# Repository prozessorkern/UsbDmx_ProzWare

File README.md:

# UsbDmx_ProzWare

Here you find the refactored hardware development (schematics and layout) of USB DMX from http://www.digital-enlightenment.de/usbdmx.htm.

Credit goes to Michael Dreschmann from http://www.digital-enlightenment.de.

This repo adds KiCad schematics and layout in SMD technology with a complete board design with onboard XLR connectors.

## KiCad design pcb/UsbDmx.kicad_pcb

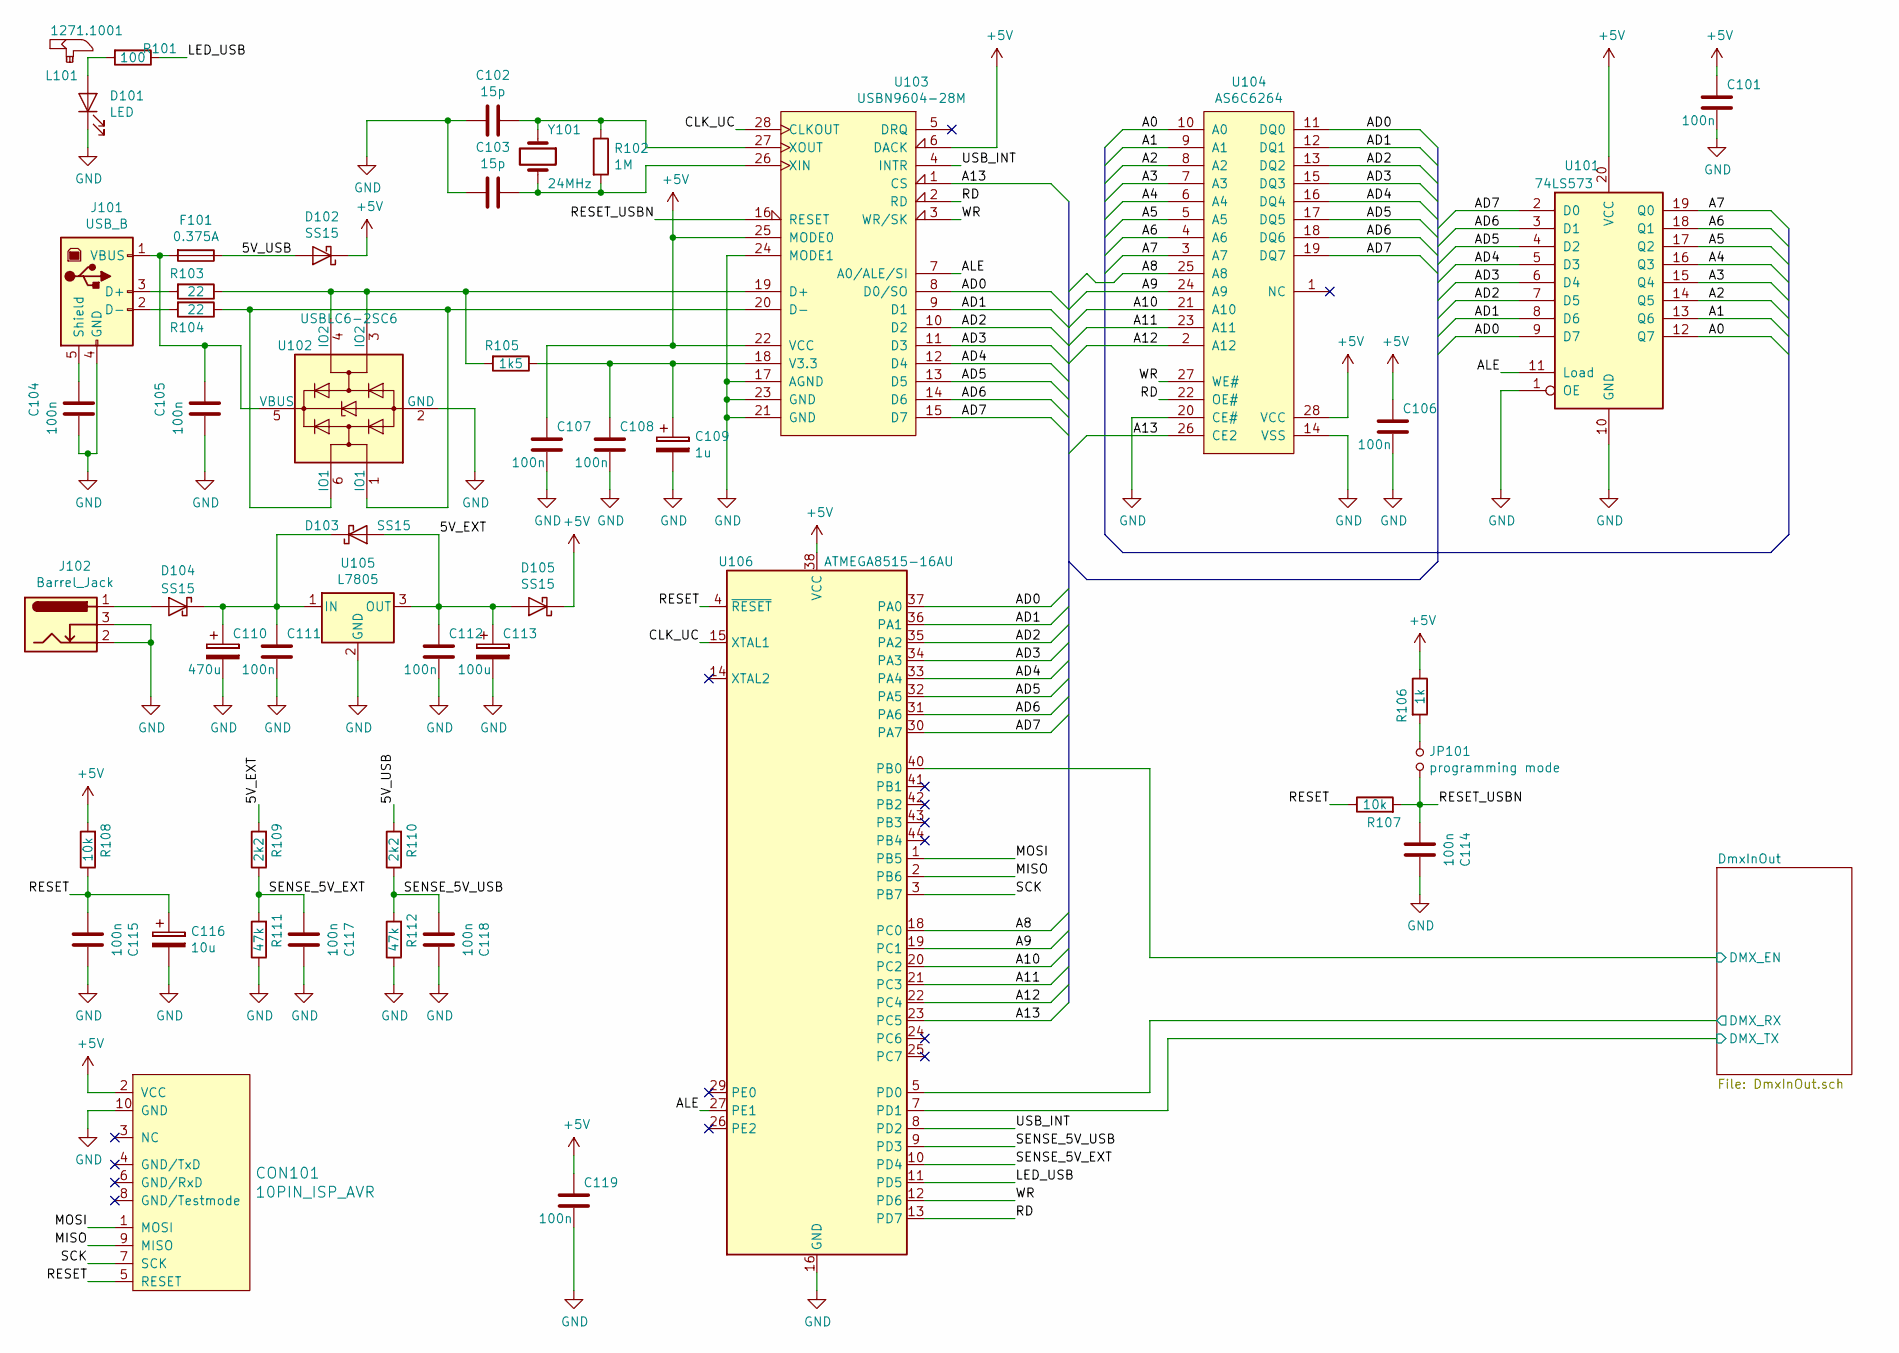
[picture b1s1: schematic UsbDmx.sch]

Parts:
C101, C106, C107, C108, C112, C114, C115, C117, C118, C119: 100n; C_0603_1608Metric_Pad1.05x0.95mm_HandSolder
C102, C103: 15p; C_0603_1608Metric_Pad1.05x0.95mm_HandSolder
C104, C105, C111: 100n; C_0805_2012Metric_Pad1.15x1.40mm_HandSolder
C109: 1u; CP_Radial_D4.0mm_P1.50mm
C110: 470u; CP_Radial_D10.0mm_P5.00mm
C113: 100u; CP_Radial_D6.3mm_P2.50mm
C116: 10u; CP_Radial_D5.0mm_P2.00mm
CON101: 10PIN_ISP_AVR; TC2050-IDC
D101: LED; LED_SMD_0603
D102, D103, D104, D105: SS15; D_SMA_Handsoldering
F101: 0.375A; Fuse_1206_3216Metric_Pad1.42x1.75mm_HandSolder
J101: USB_B; USB_B_OST_USB-B1HSxx_Horizontal
J102: Barrel_Jack; BARREL_JACK_CLIFF
JP101: programming mode; PinHeader_1x02_P2.54mm_Vertical
L101: 1271.1001
R101: 100; R_0603_1608Metric_Pad1.05x0.95mm_HandSolder
R102: 1M; R_0603_1608Metric_Pad1.05x0.95mm_HandSolder
R103, R104: 22; R_0603_1608Metric_Pad1.05x0.95mm_HandSolder
R105: 1k5; R_0603_1608Metric_Pad1.05x0.95mm_HandSolder
R106: 1k; R_0603_1608Metric_Pad1.05x0.95mm_HandSolder
R107, R108: 10k; R_0603_1608Metric_Pad1.05x0.95mm_HandSolder
R109, R110: 2k2; R_0603_1608Metric_Pad1.05x0.95mm_HandSolder
R111, R112: 47k; R_0603_1608Metric_Pad1.05x0.95mm_HandSolder
U101: 74LS573; SOIC-20W_7.5x12.8mm_P1.27mm
U102: USBLC6-2SC6; SOT-23-6
U103: USBN9604-28M; SOIC-28W_7.5x17.9mm_P1.27mm
U104: AS6C6264; SOIC-28W_8.7x18.7mm_Pitch1.27mm
U105: L7805; TO-263-2
U106: ATMEGA8515-16AU; TQFP-44_10x10mm_P0.8mm
Y101: 24MHz; Crystal_HC49-U_Vertical

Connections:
+5V: C101.1, C106.1, C107.1, C119.1, CON101.2 (VCC), D102.1 (K), D105.1 (K), R106.1, R108.2, U101.20 (VCC), U103.6 (DACK), U103.22 (VCC), U103.25 (MODE0), U104.28 (VCC), U106.38 (VCC); also elsewhere on the board
/5V_EXT: C112.1, C113.1, D103.2 (A), D105.2 (A), R109.2, U105.3 (OUT)
/5V_USB: D102.2 (A), F101.1, R110.2
/A0: U101.12 (Q7), U104.10 (A0)
/A1: U101.13 (Q6), U104.9 (A1)
/A2: U101.14 (Q5), U104.8 (A2)
/A3: U101.15 (Q4), U104.7 (A3)
/A4: U101.16 (Q3), U104.6 (A4)
/A5: U101.17 (Q2), U104.5 (A5)
/A6: U101.18 (Q1), U104.4 (A6)
/A7: U101.19 (Q0), U104.3 (A7)
/A8: U104.25 (A8), U106.18 (PC0)
/A9: U104.24 (A9), U106.19 (PC1)
/A10: U104.21 (A10), U106.20 (PC2)
/A11: U104.23 (A11), U106.21 (PC3)
/A12: U104.2 (A12), U106.22 (PC4)
/A13: U103.1 (CS), U104.26 (CE2), U106.23 (PC5)
/AD0: U101.9 (D7), U103.8 (D0/SO), U104.11 (DQ0), U106.37 (PA0)
/AD1: U101.8 (D6), U103.9 (D1), U104.12 (DQ1), U106.36 (PA1)
/AD2: U101.7 (D5), U103.10 (D2), U104.13 (DQ2), U106.35 (PA2)
/AD3: U101.6 (D4), U103.11 (D3), U104.15 (DQ3), U106.34 (PA3)
/AD4: U101.5 (D3), U103.12 (D4), U104.16 (DQ4), U106.33 (PA4)
/AD5: U101.4 (D2), U103.13 (D5), U104.17 (DQ5), U106.32 (PA5)
/AD6: U101.3 (D1), U103.14 (D6), U104.18 (DQ6), U106.31 (PA6)
/AD7: U101.2 (D0), U103.15 (D7), U104.19 (DQ7), U106.30 (PA7)
/ALE: U101.11 (Load), U103.7 (A0/ALE/SI), U106.27 (PE1)
/CLK_UC: U103.28 (CLKOUT), U106.15 (XTAL1)
/DmxInOut/DMX_EN: U106.40 (PB0); also elsewhere on the board
/DmxInOut/DMX_RX: U106.5 (PD0); also elsewhere on the board
/DmxInOut/DMX_TX: U106.7 (PD1); also elsewhere on the board
/LED_USB: R101.1, U106.11 (PD5)
/MISO: CON101.9 (MISO), U106.2 (PB6)
/MOSI: CON101.1 (MOSI), U106.1 (PB5)
/RD: U103.2 (RD), U104.22 (OE#), U106.13 (PD7)
/RESET: C115.2, C116.1, CON101.5 (RESET), R107.1, R108.1, U106.4 (~RESET)
/RESET_USBN: C114.2, JP101.2, R107.2, U103.16 (RESET)
/SCK: CON101.7 (SCK), U106.3 (PB7)
/SENSE_5V_EXT: C117.2, R109.1, R111.2, U106.10 (PD4)
/SENSE_5V_USB: C118.2, R110.1, R112.2, U106.9 (PD3)
/USB_INT: U103.4 (INTR), U106.8 (PD2)
/WR: U103.3 (WR/SK), U104.27 (WE#), U106.12 (PD6)
GND: C101.2, C102.2, C103.2, C104.2, C105.2, C106.2, C107.2, C108.2, C109.2, C110.2, C111.2, C112.2, C113.2, C114.1, C115.1, C116.2, C117.1, C118.1, C119.2, CON101.10 (GND), D101.1 (K), J101.4 (GND), J102.2, J102.3, R111.1, R112.1, U101.1 (OE), U101.10 (GND), U102.2 (GND), U103.17 (AGND), U103.21 (GND), U103.23 (GND), U103.24 (MODE1), U104.14 (VSS), U104.20 (CE#), U105.2 (GND), U106.16 (GND); also elsewhere on the board
unnamed: C102.1, R102.1, U103.27 (XOUT), Y101.1
unnamed: C103.1, R102.2, U103.26 (XIN), Y101.2
unnamed: C104.1, J101.5 (Shield)
unnamed: C105.1, F101.2, J101.1 (VBUS), U102.5 (VBUS)
unnamed: C108.1, C109.1, R105.1, U103.18 (V3.3)
unnamed: C110.1, C111.1, D103.1 (K), D104.1 (K), U105.1 (IN)
unnamed: D101.2 (A), R101.2
unnamed: D104.2 (A), J102.1
unnamed: J101.2 (D-), R104.2
unnamed: J101.3 (D+), R103.2
unnamed: JP101.1, R106.2
unnamed: R103.1, R105.2, U102.3 (IO2), U102.4 (IO2), U103.19 (D+)
unnamed: R104.1, U102.1 (IO1), U102.6 (IO1), U103.20 (D-)

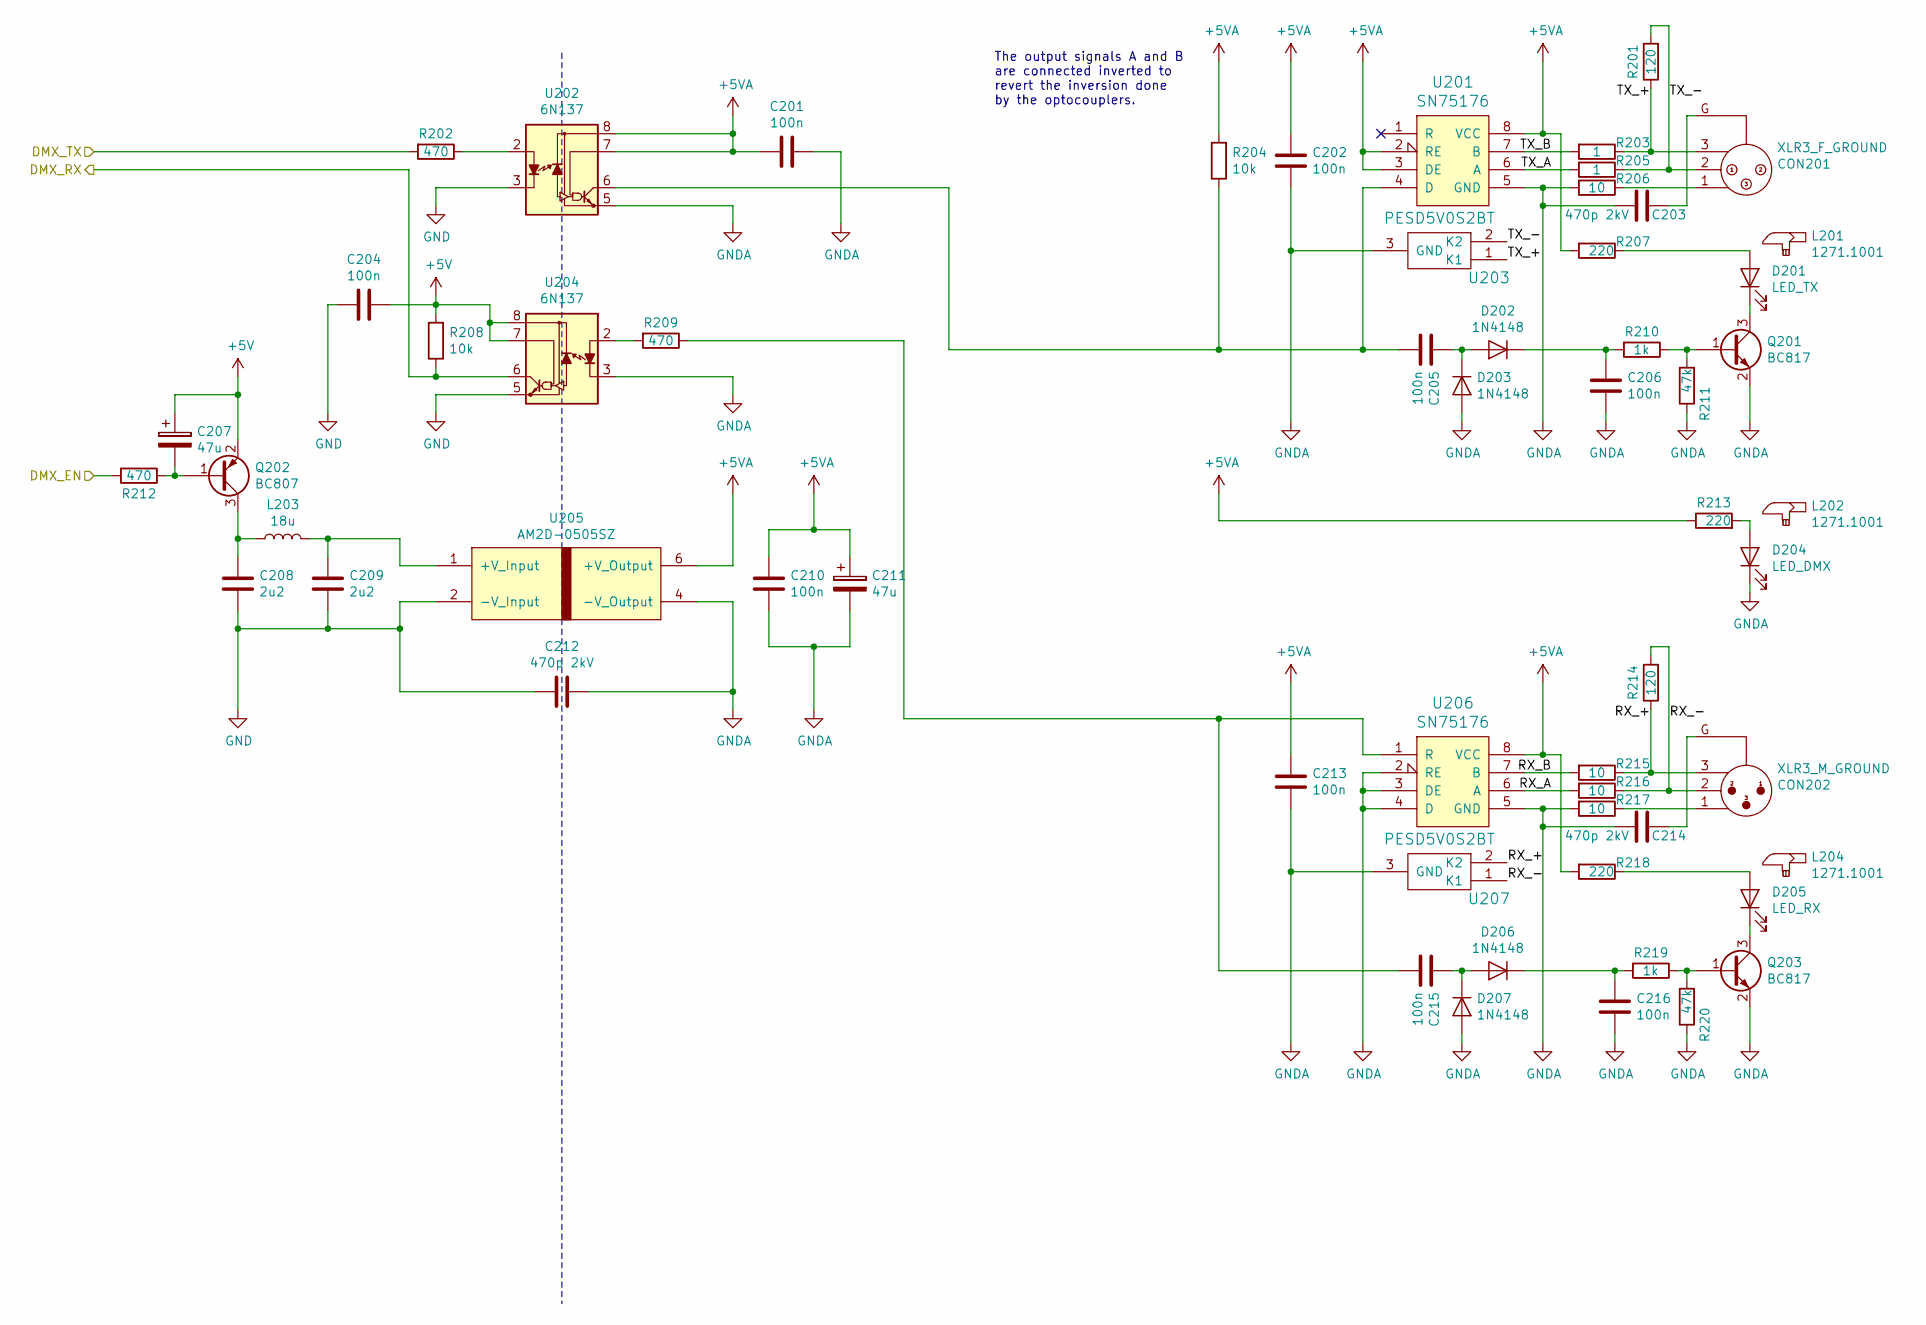
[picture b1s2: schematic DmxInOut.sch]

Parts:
C201, C202, C204, C205, C206, C210, C213, C215, C216: 100n; C_0603_1608Metric_Pad1.05x0.95mm_HandSolder
C203, C212, C214: 470p 2kV; C_Disc_D7.5mm_W5.0mm_P7.50mm
C207, C211: 47u; CP_Radial_D5.0mm_P2.00mm
C208, C209: 2u2; C_0805_2012Metric_Pad1.15x1.40mm_HandSolder
CON201: XLR3_F_GROUND; NC3FAH2_XLR_F
CON202: XLR3_M_GROUND; NC3MAH_XLR_M
D201: LED_TX; LED_SMD_0603
D202, D203, D206, D207: 1N4148; D_MiniMELF
D204: LED_DMX; LED_SMD_0603
D205: LED_RX; LED_SMD_0603
L201, L202, L204: 1271.1001
L203: 18u; inductor_1812
Q201, Q203: BC817; SOT-23
Q202: BC807; SOT-23
R201, R214: 120; R_MiniMELF_MMA-0204
R202, R209, R212: 470; R_0603_1608Metric_Pad1.05x0.95mm_HandSolder
R203, R205: 1; R_MiniMELF_MMA-0204
R204, R208: 10k; R_0603_1608Metric_Pad1.05x0.95mm_HandSolder
R206, R215, R216, R217: 10; R_MiniMELF_MMA-0204
R207, R213, R218: 220; R_0603_1608Metric_Pad1.05x0.95mm_HandSolder
R210, R219: 1k; R_0603_1608Metric_Pad1.05x0.95mm_HandSolder
R211, R220: 47k; R_0603_1608Metric_Pad1.05x0.95mm_HandSolder
U201, U206: SN75176; SO-8_3.9x4.9mm_P1.27mm
U202, U204: 6N137; GULLWING_8
U203, U207: PESD5V0S2BT; SOT-23_Handsoldering
U205: AM2D-0505SZ; SIP7

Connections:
+5V: C204.1, C207.1, Q202.2 (E), R208.2, U204.7, U204.8; also elsewhere on the board
+5VA: C201.2, C202.2, C210.2, C211.1, C213.2, R204.2, R207.2, R213.1, R218.2, U201.2 (RE), U201.3 (DE), U201.8 (VCC), U202.7, U202.8, U205.6 (+V_Output), U206.8 (VCC)
/DmxInOut/DMX_EN: R212.2; also elsewhere on the board
/DmxInOut/DMX_RX: R208.1, U204.6; also elsewhere on the board
/DmxInOut/DMX_TX: R202.2; also elsewhere on the board
/DmxInOut/RX_+: CON202.3, R214.1, R215.1, U207.2 (K2)
/DmxInOut/RX_-: CON202.2, R214.2, R216.1, U207.1 (K1)
/DmxInOut/RX_A: R216.2, U206.6 (A)
/DmxInOut/RX_B: R215.2, U206.7 (B)
/DmxInOut/TX_+: CON201.3, R201.1, R203.1, U203.1 (K1)
/DmxInOut/TX_-: CON201.2, R201.2, R205.1, U203.2 (K2)
/DmxInOut/TX_A: R205.2, U201.6 (A)
/DmxInOut/TX_B: R203.2, U201.7 (B)
GND: C204.2, C208.2, C209.2, C212.2, U202.3, U204.5, U205.2 (-V_Input); also elsewhere on the board
GNDA: C201.1, C202.1, C203.2, C206.1, C210.1, C211.2, C212.1, C213.1, C214.2, C216.1, D203.2 (A), D204.1 (K), D207.2 (A), Q201.2 (E), Q203.2 (E), R206.2, R211.1, R217.2, R220.1, U201.5 (GND), U202.5, U203.3 (GND), U204.3, U205.4 (-V_Output), U206.2 (RE), U206.3 (DE), U206.4 (D), U206.5 (GND), U207.3 (GND)
unnamed: C203.1, CON201.G
unnamed: C205.1, R204.1, U201.4 (D), U202.6
unnamed: C205.2, D202.2 (A), D203.1 (K)
unnamed: C206.2, D202.1 (K), R210.2
unnamed: C207.2, Q202.1 (B), R212.1
unnamed: C208.1, L203.1, Q202.3 (C)
unnamed: C209.1, L203.2, U205.1 (+V_Input)
unnamed: C214.1, CON202.G
unnamed: C215.1, R209.1, U206.1 (R)
unnamed: C215.2, D206.2 (A), D207.1 (K)
unnamed: C216.2, D206.1 (K), R219.2
unnamed: CON201.1, R206.1
unnamed: CON202.1, R217.1
unnamed: D201.1 (K), Q201.3 (C)
unnamed: D201.2 (A), R207.1
unnamed: D204.2 (A), R213.2
unnamed: D205.1 (K), Q203.3 (C)
unnamed: D205.2 (A), R218.1
unnamed: Q201.1 (B), R210.1, R211.2
unnamed: Q203.1 (B), R219.1, R220.2
unnamed: R202.1, U202.2
unnamed: R209.2, U204.2

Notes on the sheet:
The output signals A and B are connected inverted to revert the inversion done by the optocouplers.

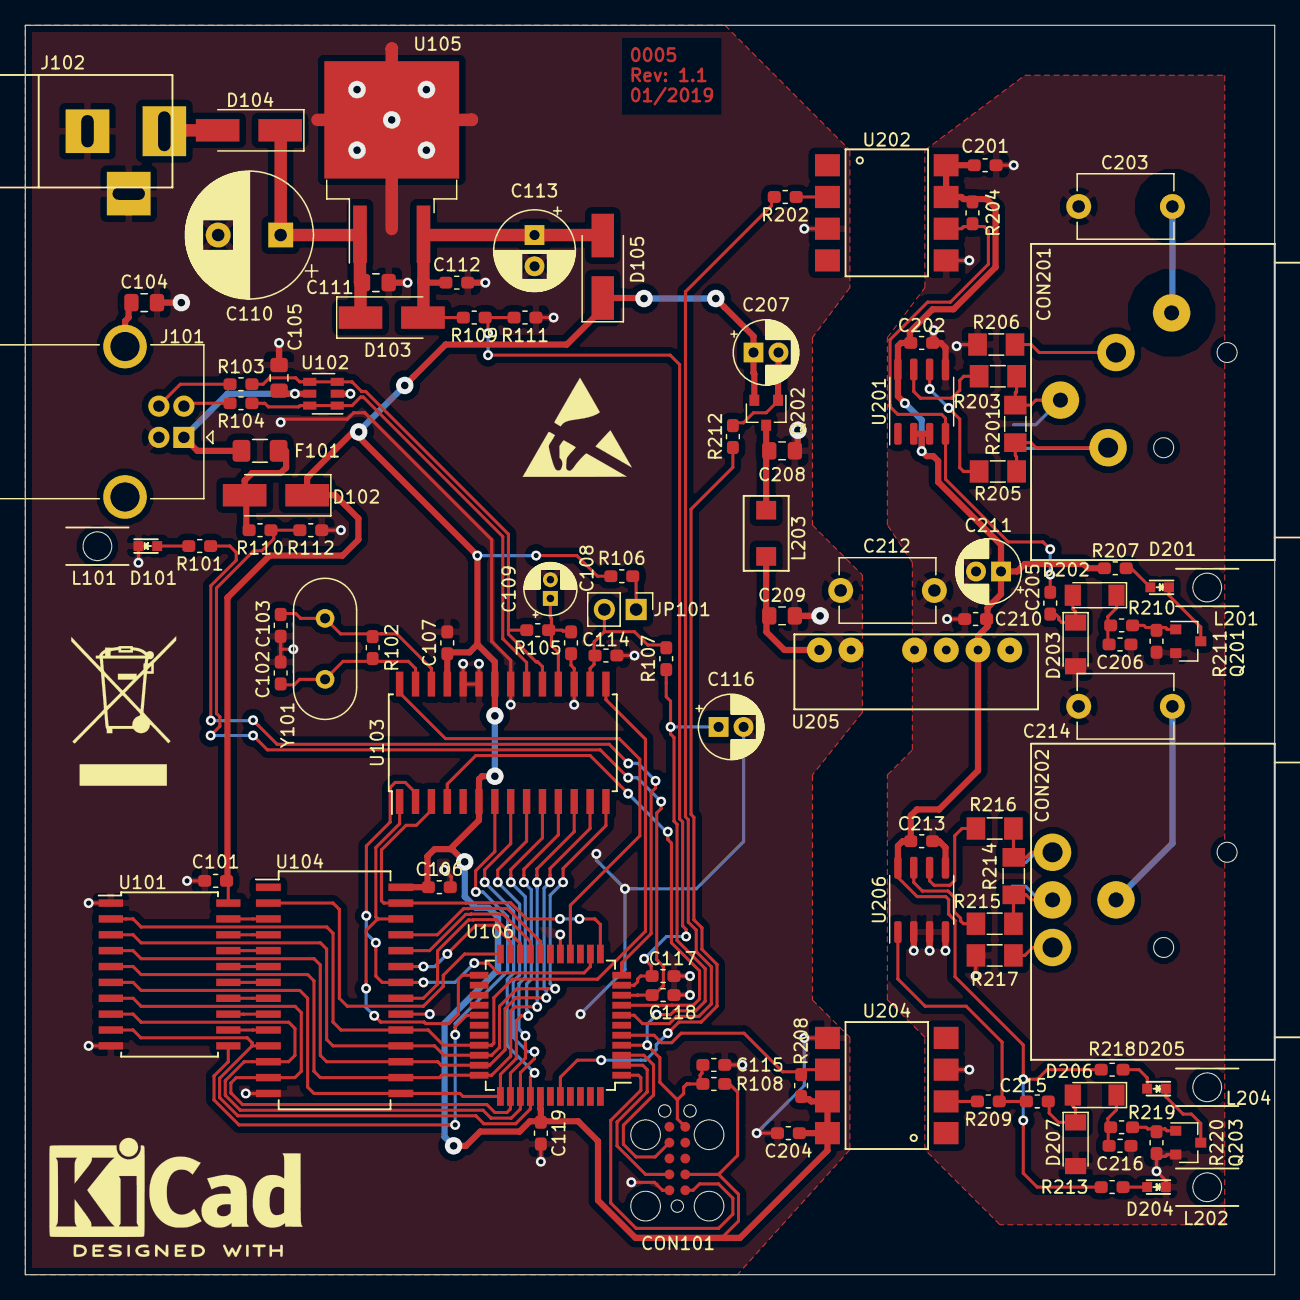
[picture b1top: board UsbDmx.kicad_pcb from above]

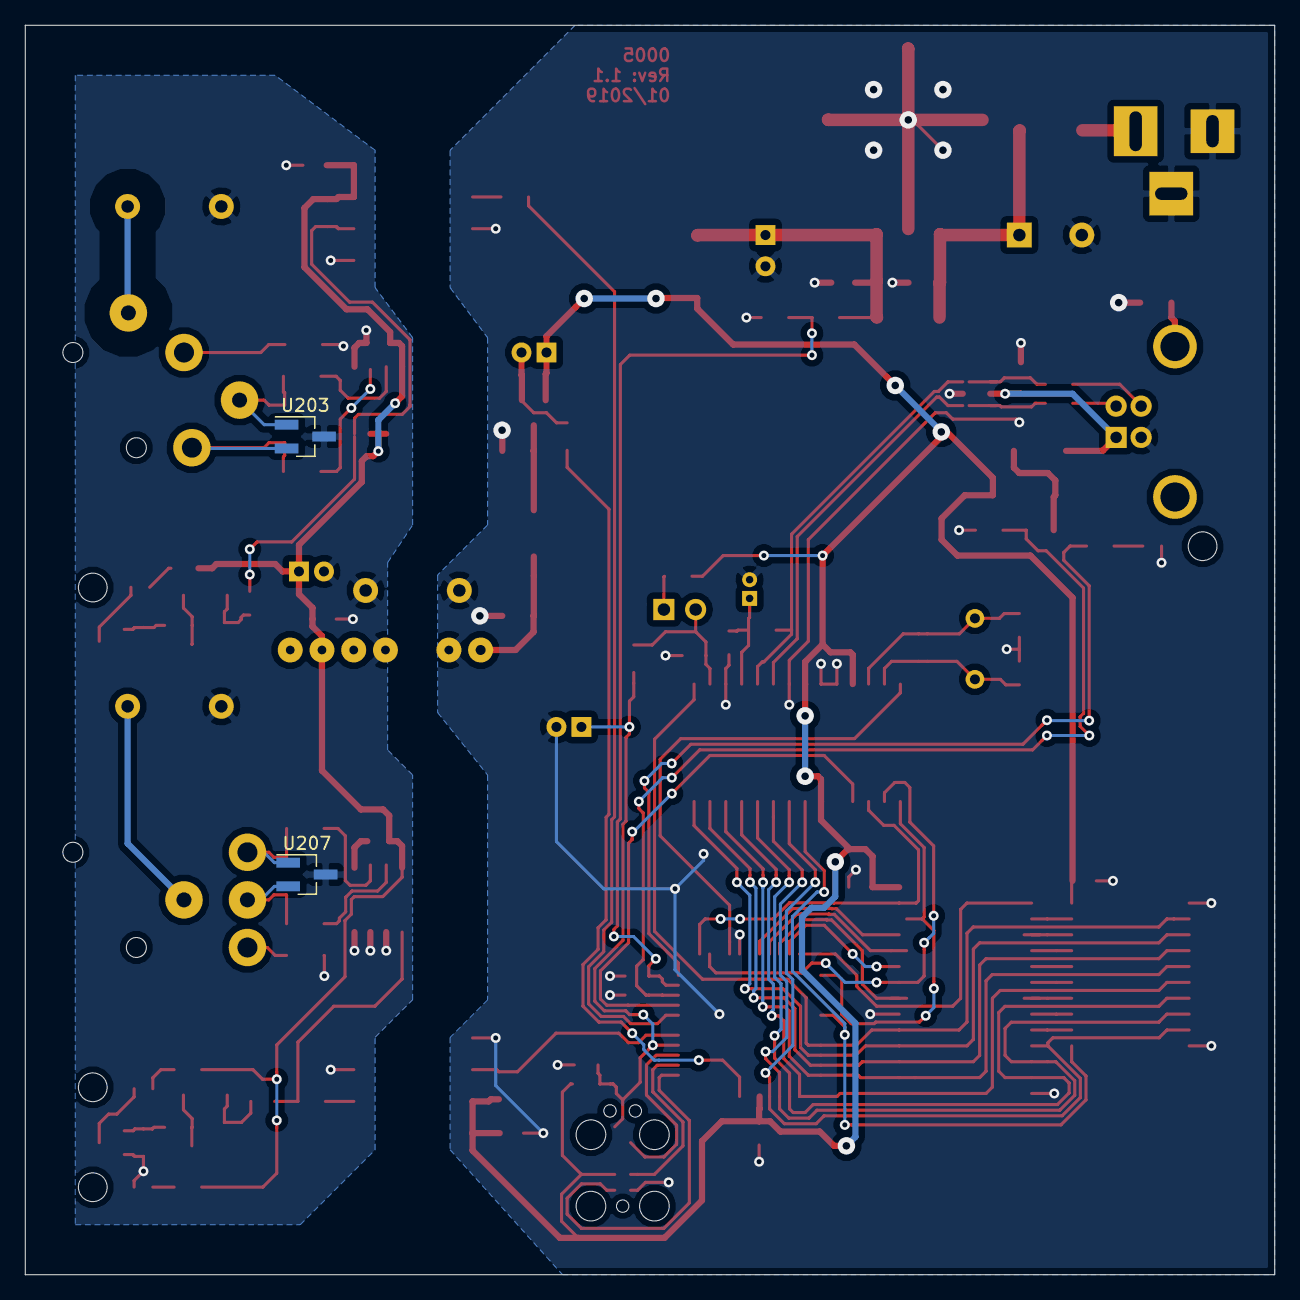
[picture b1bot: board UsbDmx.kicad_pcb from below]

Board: 2 copper layers, 100.0 x 100.0 mm, 108 parts (2 on the bottom side), 87 nets.

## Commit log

2018-11-24 Added the KiCad project with the nearly finished schematics
2018-11-25 Started footprint association
2018-11-27 finished footprint association
2018-12-18 startet layouting
    Startet to create a Layout
2018-12-20 Finished layout
    Added esd protection diodes to the dmx interface
    Routed everything
    added ground planes
    added some logos...
2018-12-24 final release 1.0
2019-01-20 Bugfixing after testing prototype
    Added a different pullup mechanism during programming to keep the USBN active during reset. Otherwise the ATmega loses its clock.
    Fixed the broken pin association of the DMX connectors.
2019-01-23 fixed XLR connectors, LEDs and Reset
2019-01-29 changed footprints to fit better the real parts
2019-01-29 fixed silkscreen
2019-02-02 Updated all KiCad symbols and footprints to the ones on the current master branch of their symbols created all documents to produce this thing
